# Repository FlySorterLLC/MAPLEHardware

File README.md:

# MAPLEHardware Repository

The MAPLE Hardware Repository contains the design files for the MAPLE fruit fly handling robot.

Build instructions: https://docs.google.com/document/d/1TA3YupyyByrOd9m6okqdpYfM0JYXHaHCEhxIdzhBA4U/edit?usp=sharing

BOM: https://docs.google.com/spreadsheets/d/1WS5JZ8TgN1G7_WdbVoJIBsS1zV8HpRZNDN9ckr8W_F8/edit?usp=sharing

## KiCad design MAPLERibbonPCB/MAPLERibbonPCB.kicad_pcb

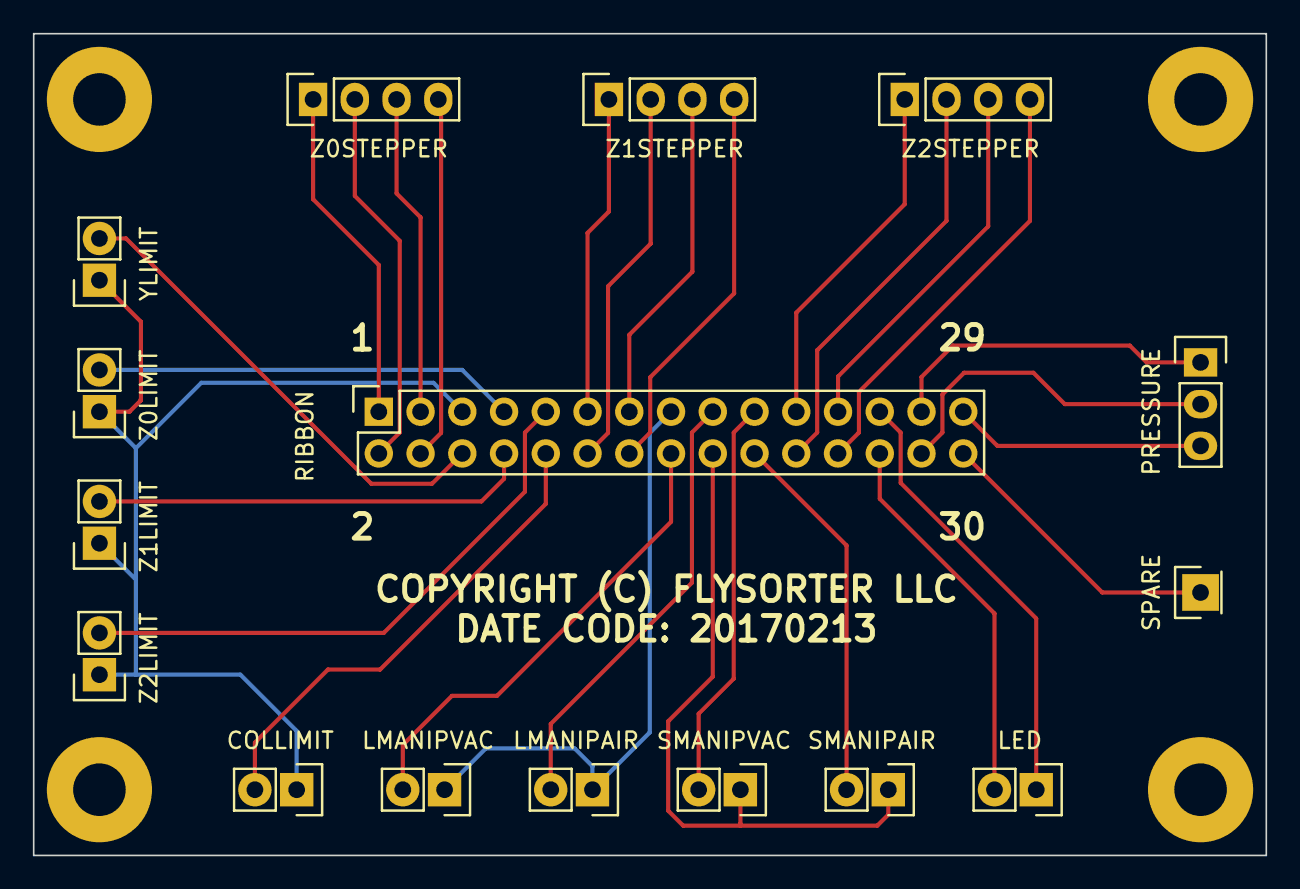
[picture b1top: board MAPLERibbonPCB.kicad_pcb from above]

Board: 2 copper layers, 75.0 x 50.0 mm, 20 parts (0 on the bottom side), 30 nets.

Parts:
P1: YLIMIT; Socket_Strip_Straight_1x02
P2: Z0STEPPER; Socket_Strip_Straight_1x04
P3: LMANIPVAC; Socket_Strip_Straight_1x02
P4: Z0LIMIT; Socket_Strip_Straight_1x02
P5: RIBBON; Socket_Strip_Straight_2x15
P6: Z1STEPPER; Socket_Strip_Straight_1x04
P7: LED; Socket_Strip_Straight_1x02
P8: LMANIPAIR; Socket_Strip_Straight_1x02
P9: Z1LIMIT; Socket_Strip_Straight_1x02
P10: SMANIPVAC; Socket_Strip_Straight_1x02
P11: PRESSURE; Socket_Strip_Straight_1x03
P12: Z2STEPPER; Socket_Strip_Straight_1x04
P13: Z2LIMIT; Socket_Strip_Straight_1x02
P14: SPARE; Socket_Strip_Straight_1x01
P15: SMANIPAIR; Socket_Strip_Straight_1x02
P16: COLLIMIT; Socket_Strip_Straight_1x02
P17, P18, P19, P20: MOUNT; MountingHole_3.2mm_M3_Pad

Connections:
/CollisionLimit: P5.10, P16.2
/LEDGND: P5.25, P7.1
/LEDVCC: P5.26, P7.2
/LManipAir: P5.17, P8.2
/LManipGrounds: P3.1, P5.15, P8.1
/LManipVac: P3.2, P5.16
/PressureGND: P5.27, P11.1
/PressureSignal: P5.29, P11.3
/PressureVCC: P5.28, P11.2
/SManipAir: P5.20, P15.2
/SManipGrounds: P5.18, P10.1, P15.1
/SManipVac: P5.19, P10.2
/SwitchGrounds: P1.1, P4.1, P5.5, P9.1, P13.1, P16.1
/YLimit: P1.2, P5.6
/Z0Limit: P4.2, P5.7
/Z0Stepper0: P2.1, P5.1
/Z0Stepper1: P2.2, P5.2
/Z0Stepper2: P2.3, P5.3
/Z0Stepper3: P2.4, P5.4
/Z1Limit: P5.8, P9.2
/Z1Stepper0: P5.11, P6.1
/Z1Stepper1: P5.12, P6.2
/Z1Stepper2: P5.13, P6.3
/Z1Stepper3: P5.14, P6.4
/Z2Limit: P5.9, P13.2
/Z2Stepper0: P5.21, P12.1
/Z2Stepper1: P5.22, P12.2
/Z2Stepper2: P5.23, P12.3
/Z2Stepper3: P5.24, P12.4
unnamed: P5.30, P14.1

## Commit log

2016-12-15 Update README.md
    Add links to BOM & build instructions
2016-12-22 Add v1 drawings
    Added drawings folder and exported (DXF & PDF) drawings.
2016-12-22 Added STLs
    3d printed part files for Santa Fe
2016-12-27 X axis bearing mod drawing
2017-03-08 Update spm for shoulder screws
    Update to the design of the small part manipulator manifold to use
    shoulder screws (McMaster 90265A122) instead of regular M3 bolts.
2017-12-20 Adding SW and KiCAD files
    Uploading Solidworks (Pack & Go) and KiCAD files to repo.
2017-12-20 Renaming files - no more "Santa Fe", no more version numbers in filenames.
2017-12-20 Gitignore in Solidworks directory
    Make sure Solidworks working/backup files don't get added to repo.
2017-12-20 Add bellows mold
    Add solidworks and STLs for bellows mold parts.
2017-12-20 Bellows update
2018-07-25 Add large manipulator manifold STL
    The large manipulator manifold can be machined or 3d printed. STL was missing.
2018-09-03 Update drawings to include holes in Z plate
    Drawings had already been up-revved, just not checked in.
2018-09-06 Added EndPanel and WorkSurface drawings
    Solidworks Drawings and PDFs for End Panel and Work Surface (plus
    Solidworks part for work surface).

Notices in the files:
MAPLERibbonPCB/MAPLERibbonPCB.kicad_pcb:
COPYRIGHT (C) FLYSORTER LLC
